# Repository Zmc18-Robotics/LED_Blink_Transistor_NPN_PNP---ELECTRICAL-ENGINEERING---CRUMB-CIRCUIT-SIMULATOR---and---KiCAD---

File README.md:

# LED_Blink Transistor NPN PNP - ELECTRICAL ENGINEERING - CRUMB CIRCUIT SIMULATOR - KiCAD
Controllable LED blink with transistors

---

# Here The Pictures :

Here you can edit the resistor to control the frequency

# Electrical Circuit :

---

# Description

LED blink using Transistor systems, NPN and PNP

in the picture we can see 2 transistors, the left one is PNP and the right on in NPN. you can see all in the circuit and the picture, to control the frequency, you can change the resistor ohms or just change the capacitor

Here the materials :
- Transistor NPN x1
- Transistor PNP x1
- Resistor 1000Ω x1
- Resistor 1000000Ω x1
- Resistor 10Ω x1 ( you can use 2Ω, or 20Ω, or anything, its editable for the frequency, more smaller ohms = more faster frequency )
- LED pin x1 ( you can add again or modify it if you want )
- Capacitor 2.2µF x1
- Breadboard x1
- Power Supply x1
  
---

Just use the Electrical logic systems~
Have fun~ ^^

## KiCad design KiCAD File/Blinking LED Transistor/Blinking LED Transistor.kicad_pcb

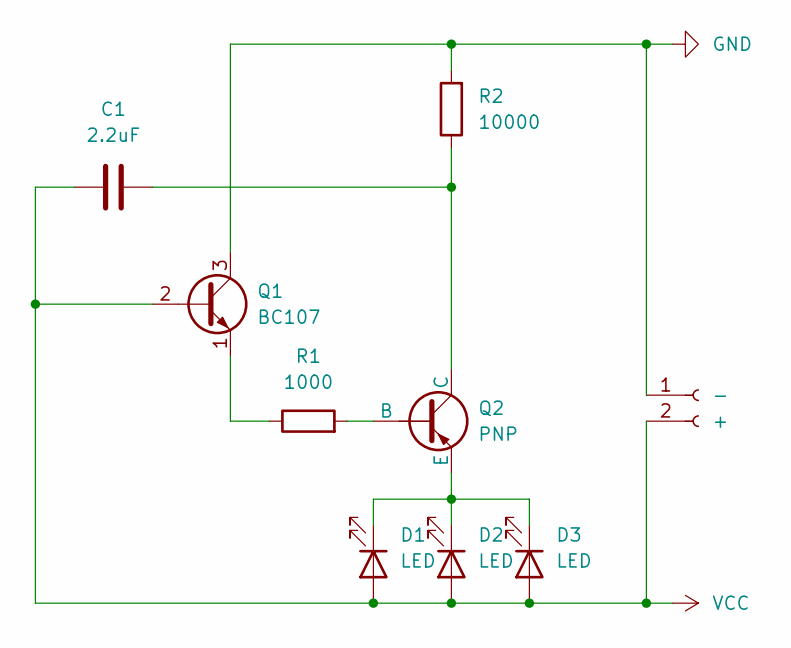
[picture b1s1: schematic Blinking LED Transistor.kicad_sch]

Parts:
-: +; PinHeader_1x02_P2.54mm_Vertical
C1: 2.2uF; CP_Radial_D6.3mm_P2.50mm
D1, D2, D3: LED; LED_D5.0mm
Q1: BC107; TO-18-3
Q2: PNP; TO-92L_Inline
R1: 1000; C_0805_2012Metric
R2: 10000; C_01005_0402Metric

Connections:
GND: -.1, Q1.3 (C), R2.2
unnamed: D1.1 (K), D2.1 (K), D3.1 (K), Q2.3 (E)
unnamed: Q1.1 (E), R1.1
unnamed: Q2.2 (B), R1.2
unnamed: C1.2, Q2.1 (C), R2.1
VCC: -.2, C1.1, D1.2 (A), D2.2 (A), D3.2 (A), Q1.2 (B)

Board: 2 copper layers, 9 parts (0 on the bottom side), 6 nets, no tracks yet.
